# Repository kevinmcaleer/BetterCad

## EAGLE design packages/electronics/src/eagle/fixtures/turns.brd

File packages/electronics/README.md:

# @bettercad/electronics

The electronics design model (epic #606): components, schematic sheets, the board, and the logic that ties them
together. Framework-free: no React, no three.js, no DOM.

- `model.ts`: the types saved in a `.bcad` file under `electronics`.
- `geom.ts`: 2D helpers. Millimetres, x to the right, y up.
- `nets.ts`: works out the nets from wires, labels, junctions and power symbols.
- `sync.ts`: the change list that keeps the board in step with the schematic.

See `docs/electronics.md`.

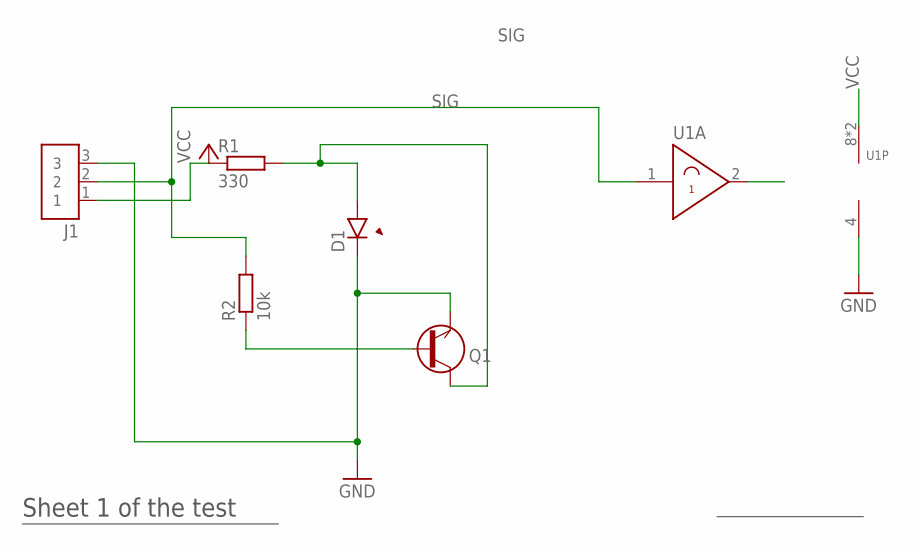
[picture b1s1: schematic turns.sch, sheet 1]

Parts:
D1: red; LED5MM
J1: HDR3
Q1: NPN-BC817SOT23; SOT23
R1: 330; R0805
R2: 10k; R0805
U1: DUALBUFD; SO8

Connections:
GND: D1.K (C), J1.3, Q1.2 (E), U1.4 (GND); also elsewhere on the board
MID: U1.2 (OUT); also elsewhere on the board
unnamed: D1.A, Q1.3 (C), R1.2
unnamed: Q1.1 (B), R2.1
SIG: J1.2, R2.2, U1.1 (IN)
VCC: J1.1, R1.1, U1.7 (VCC), U1.8 (VCC)

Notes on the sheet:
Sheet 1 of the test

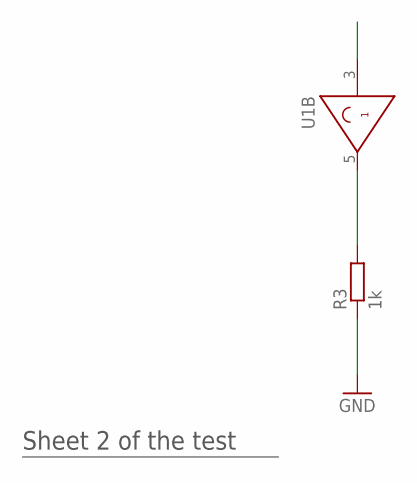
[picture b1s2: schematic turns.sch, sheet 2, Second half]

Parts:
R3: 1k; R0805
U1: DUALBUFD; SO8

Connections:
GND: R3.1; also elsewhere on the board
MID: U1.3 (IN); also elsewhere on the board
OUT: R3.2, U1.5 (OUT)

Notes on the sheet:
Sheet 2 of the test

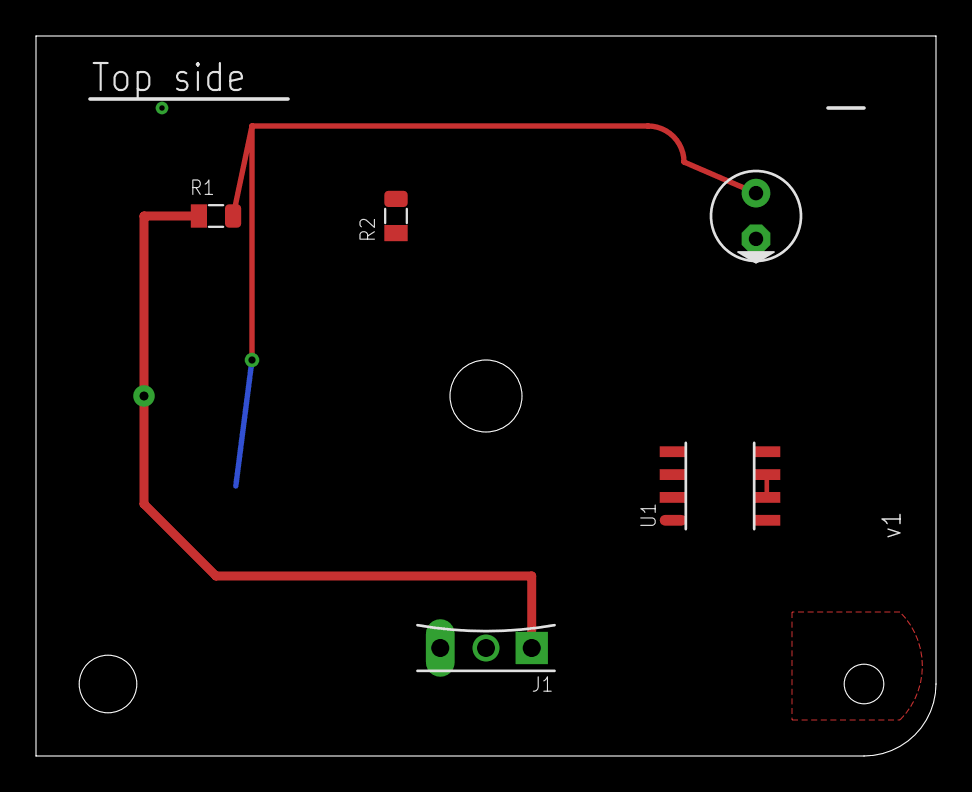
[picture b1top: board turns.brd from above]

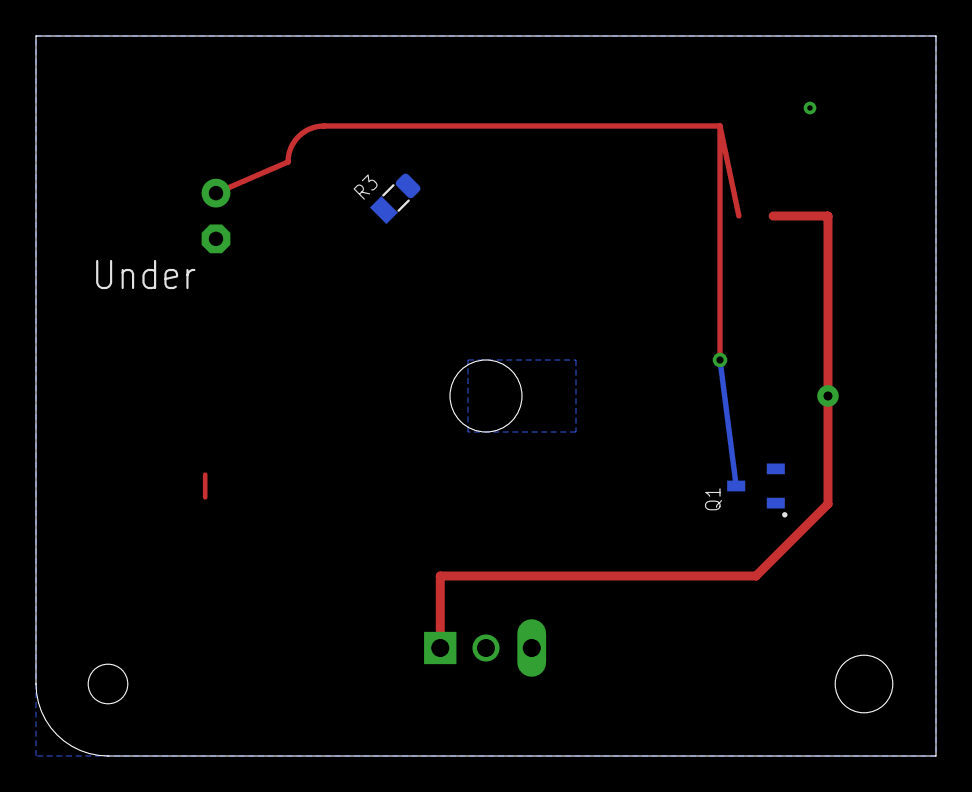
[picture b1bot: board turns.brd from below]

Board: 3 copper layers, 50.0 x 40.0 mm, 9 parts (2 on the bottom side), 7 nets.

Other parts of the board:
H1: HOLE3
LOGO1: LOGO
